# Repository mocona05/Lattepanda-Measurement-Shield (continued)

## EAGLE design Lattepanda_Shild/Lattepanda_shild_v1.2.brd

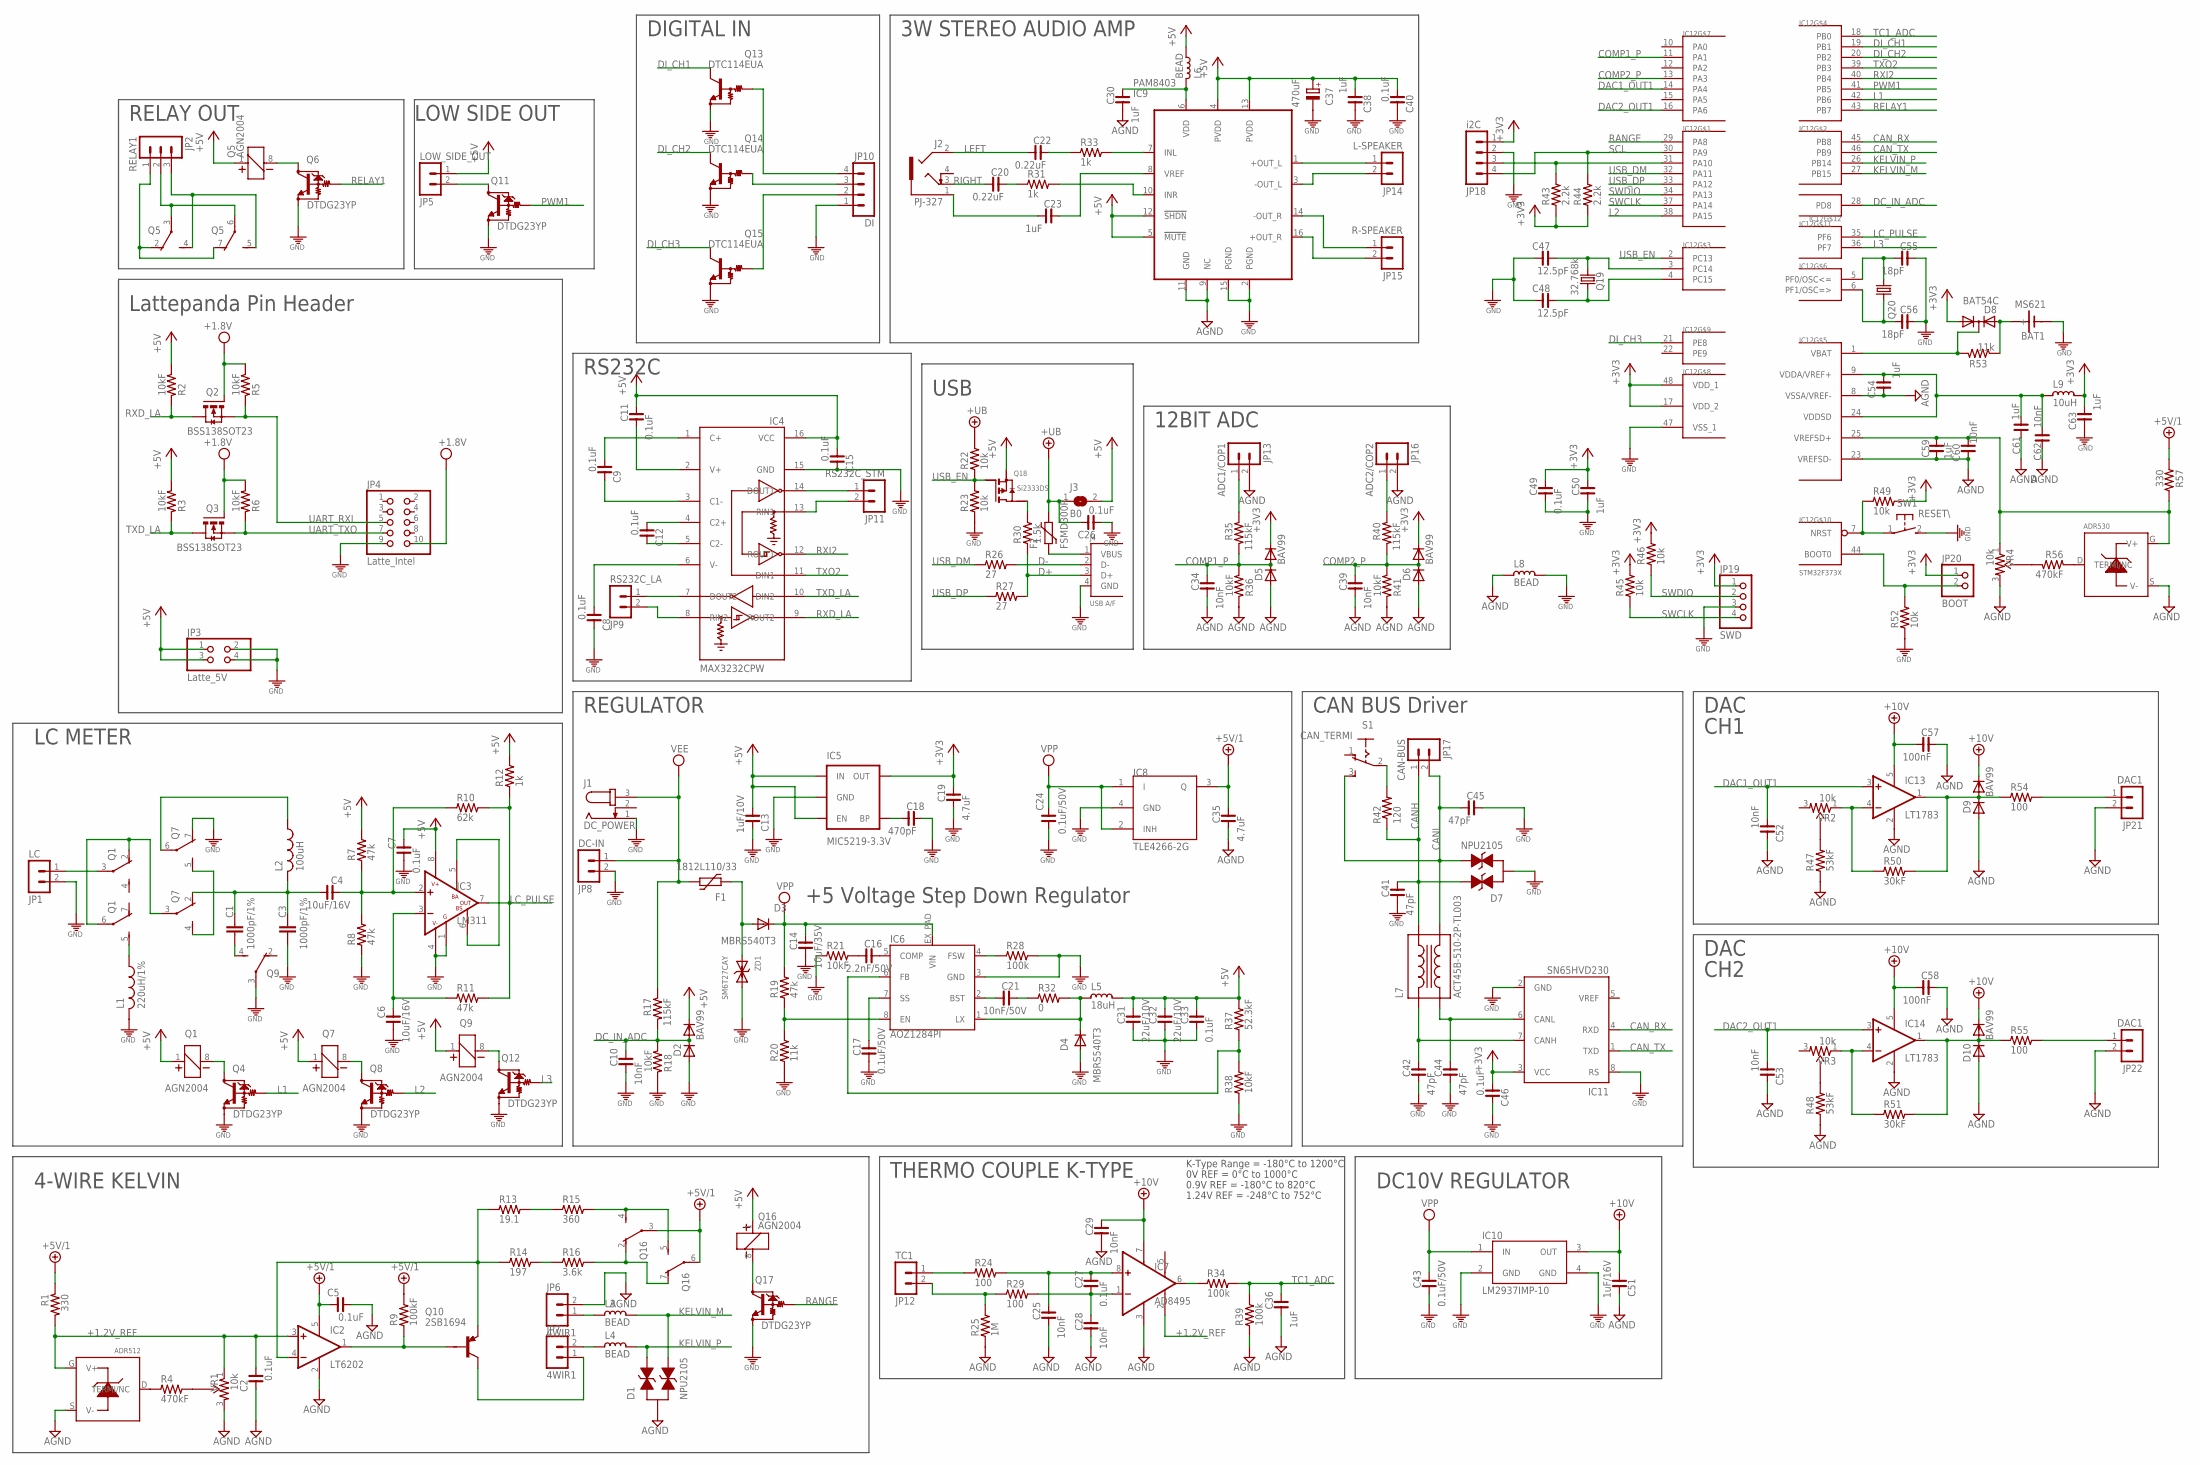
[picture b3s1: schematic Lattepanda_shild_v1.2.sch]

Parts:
BAT1: MS621
C1, C3: 1000pF/1%; C050-025X075
C2, C5, C7, C8, C9, C11, C12, C15, C26, C27, C33, C40, C46, C49: 0.1uF; C0603
C4, C6: 10uF/16V; C3216
C10, C25, C28, C29, C34, C39, C52, C53, C60, C62: 10nF; C0603
C13: 1uF/10V; C0603
C14: 10uF/35V; C3225
C16: 2.2nF/50V; C0603
C17, C43: 0.1uF/50V; C0603
C18: 470pF; C0603
C19, C35: 4.7uF; C2012
C20, C22: 0.22uF; C0603
C21: 10nF/50V; C0603
C23, C30, C36, C38, C50, C54, C59, C61, C63: 1uF; C0603
C24: 0.1uF/50V; C1608-
C31, C32: 22uF/10V; C3216
C37: 470uF; D/7343-31W
C41, C42, C44, C45: 47pF; C0603
C47, C48: 12.5pF; C0603
C51: 1uF/16V; C0603
C55, C56: 18pF; C0603
C57, C58: 100nF; C0603
D1, D7: NPU2105; SOT23
D2, D5, D6, D9, D10: BAV99; SOT23
D3, D4: MBRS540T3; SMC
D8: BAT54C; SOT23
F1: 1812L110/33; 1812L
F2: FSMD300R; 1812L
IC1: ADR512; SOT23
IC2: LT6202; SOT23-5L
IC3: LM311; SO8
IC4: MAX3232CPW; PW_R-PDSO-G16
IC5: MIC5219-3.3V; SOT23-5
IC6: AOZ1284PI; S08-EP1
IC7: AD8495; MSOP8
IC8: TLE4266-2G; SOT223-4
IC9: PAM8403; SOIC16N
IC10: LM2937IMP-10; SOT223
IC11: SN65HVD230; SO8
IC12: STM32F373X; TQFP48
IC13, IC14: LT1783; SOT23-5
IC15: ADR530; SOT23
J1: DC_POWER; SPC4077
J2: PJ-327; PJ-327-2
J3: B0; SJ
J4: USB A/F; USB_AF_SIDE
JP1: LC; ED350V-02P
JP2: RELAY1; ED350V-03P
JP3: Latte_5V; 2X02
JP4: Latte_Intel; 2X05M
JP5: LOW_SIDE_OUT; ED350V-02P
JP6, JP7: 4WIR1; ED350V-02P
JP8: DC-IN; ED350V-02P
JP9: RS232C_LA; ED350V-02P
JP10: DI; 53047-04
JP11: RS232C_STM; ED350V-02P
JP12: TC1; ED350V-02P
JP13: ADC1/COP1; ED350V-02P
JP14: L-SPEAKER; ED350V-02P
JP15: R-SPEAKER; ED350V-02P
JP16: ADC2/COP2; ED350V-02P
JP17: CAN-BUS; ED350V-02P
JP18: i2C; MOLEX5267-04
JP19: SWD; 1X04M
JP20: BOOT; 1X02M
JP21, JP22: DAC1; ED350V-02P
L1: 220uH/1%; 0207/2V
L2: 100uH; 0207/2V
L3, L4, L8: BEAD; L0603
L5: 18uH; SHP1260P-F
L6: BEAD; L0805
L7: ACT45B-510-2P-TL003; ACT45B
L9: 10uH; L0805
Q1, Q5, Q7, Q9, Q16: AGN2004; ANG200X
Q2, Q3: BSS138SOT23; SOT23
Q4, Q6, Q8, Q11, Q12, Q17: DTDG23YP; MPT3
Q10: 2SB1694; SOT323
Q13, Q14, Q15: DTC114EUA; SC59-BEC
Q18: Si2333DS; SOT23
Q19: 32.768k; MC-306
Q20: 8MHz; SMD5032
R1, R57: 330; R0603
R2, R3, R5, R6, R18, R21, R36, R38, R41: 10kF; R0603
R4, R56: 470kF; R0603
R7, R8, R11, R19: 47k; R0603
R9: 100kF; R0603
R10: 62k; R0603
R12, R31, R33: 1k; R0603
R13: 19.1; R0603
R14: 197; R0603
R15: 360; R0603
R16: 3.6k; R0603
R17, R35, R40: 115kF; R0603
R20, R53: 11k; R0603
R22, R23, R45, R46, R49, R52: 10k; R0603
R24, R29, R54, R55: 100; R0603
R25: 1M; R0603
R26, R27: 27; R0603
R28, R34, R39: 100k; R0603
R30: 1.5k; R0603
R32: 0; R0603
R37: 52.3kF; R0603
R42: 120; R0603@1
R43, R44: 2.2k; R0603
R47, R48: 53kF; R0603
R50, R51: 30kF; R0603
S1: CAN_TERMI; 255SB
SW1: RESET\; DTSM-3
VR1, VR4: 10k; 3266W
VR2, VR3: 10k; R-TRIMMER-3313J
ZD1: SM6T27CAY; SMB

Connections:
+1.2V_REF: C2.2, IC1.G (V+), IC2.3 (+IN), IC7.2 (REF), R1.2, VR1.1
+3V3: C19.1, C46.2, C49.1, C50.1, C63.2, D5.S (C), D6.S (C), D8.G (1), IC5.5 (OUT), IC11.3 (VCC), IC12.17 (VDD_2), IC12.48 (VDD_1), JP18.1, JP19.1, JP20.1, L9.1, R43.1, R44.1, R45.2, R46.2, R49.2
+5V: C7.1, C11.1, C13.2, C15.2, C31.1, C32.1, C33.1, C37.+, C38.2, C40.2, D2.S (C), IC3.8 (V+), IC4.16 (VCC), IC5.1 (IN), IC5.3 (EN), IC9.4 (PVDD), IC9.5 (!MUTE), IC9.12 (!SHDN), IC9.13 (PVDD), J3.2, JP3.1, JP3.3, JP5.1, L5.1, L6.1, Q1.1, Q5.1, Q7.1, Q9.1, Q16.1, Q18.S (SOURCE), R2.2, R3.2, R7.2, R12.2, R37.2
+5V/1: C5.1, C35.1, IC2.5 (V+), IC8.3 (Q), Q16.3, Q16.6, R1.1, R9.2, R57.1
+10V: C29.1, C51.2, C57.2, C58.2, D9.S (C), D10.S (C), IC7.7 (V+), IC10.3 (OUT), IC13.5 (V+), IC14.5 (V+)
+UB: C26.1, F2.P$2 (2), J3.1, R22.2
AGND: C2.1, C5.2, C25.2, C28.2, C29.2, C30.2, C34.2, C35.2, C36.2, C39.2, C51.1, C52.1, C53.1, C54.1, C57.1, C58.1, C59.2, C60.1, C61.1, C62.1, D1.D (PIN3), D5.G (A), D6.G (A), D9.G (A), D10.G (A), IC1.S (V-), IC2.2 (V-), IC7.3 (V-), IC9.9 (NC), IC9.11 (GND), IC12.8 (VSSA/VREF-), IC12.23 (VREFSD-), IC13.2 (V-), IC14.2 (V-), IC15.S (V-), JP6.2, JP13.2, JP16.2, JP21.2, JP22.2, L8.2, R25.1, R36.1, R39.1, R41.1, R47.1, R48.1, VR1.3, VR4.3
BOOT1: IC12.44 (BOOT0), JP20.2, R52.2
CANH: C41.1, D7.G (PIN1), JP17.1, L7.4, R42.1
CANL: C45.2, D7.S (PIN2), JP17.2, L7.3, S1.3 (S)
CAN_RX: IC11.4 (RXD), IC12.45 (PB8)
CAN_TX: IC11.1 (TXD), IC12.46 (PB9)
COMP1_P: C34.1, D5.D (AC), IC12.11 (PA1), R35.2, R36.2
COMP2_P: C39.1, D6.D (AC), IC12.13 (PA3), R40.2, R41.2
D+: J4.3 (D+), R27.2, R30.1
D-: J4.2 (D-), R26.2
DAC1_OUT1: C52.2, IC12.14 (PA4), IC13.3 (+IN)
DAC2_OUT1: C53.2, IC12.16 (PA6), IC14.3 (+IN)
DC-IN: D3.A, F1.P$1 (1), ZD1.A
DC_IN_ADC: C10.1, D2.D (AC), IC12.28 (PD8), R17.2, R18.2
DI_CH1: IC12.19 (PB1), Q13.3 (OUT)
DI_CH2: IC12.20 (PB2), Q14.3 (OUT)
DI_CH3: IC12.21 (PE8), Q15.3 (OUT)
GND: BAT1.-, C3.2, C6.2, C7.2, C8.1, C10.2, C13.1, C14.2, C15.1, C17.2, C18.1, C19.2, C24.1, C26.2, C31.2, C32.2, C33.2, C37.-, C38.1, C40.1, C41.2, C42.2, C43.2, C44.2, C45.1, C46.1, C47.1, C48.1, C49.2, C50.2, C55.1, C56.1, C63.1, D2.G (A), D4.A, D7.D (PIN3), IC3.1 (G), IC3.4 (V-), IC4.15 (GND), IC5.2 (GND), IC6.3 (GND), IC8.4 (GND), IC9.2 (PGND), IC9.15 (PGND), IC10.2 (GND), IC10.4 (GND), IC11.2 (GND), IC11.8 (RS), IC12.47 (VSS_1), J1.1, J4.4 (GND), JP1.2, JP3.2, JP3.4, JP4.9, JP8.2, JP10.1, JP18.2, JP19.3, L1.2, L8.1, Q4.EMITTER (GND), Q6.EMITTER (GND), Q7.7 (O), Q8.EMITTER (GND), Q9.3, Q11.EMITTER (GND), Q12.EMITTER (GND), Q13.1 (GND), Q14.1 (GND), Q15.1 (GND), Q17.EMITTER (GND), R8.1, R18.1, R20.1, R21.1, R23.1, R28.2, R38.1, R52.1, SW1.2, ZD1.C (K)
KELVIN_M: D1.S (PIN2), IC12.27 (PB15), L3.1
KELVIN_P: D1.G (PIN1), IC12.26 (PB14), L4.1
L1: IC12.42 (PB6), Q4.BASE (IN)
L2: IC12.38 (PA15), Q8.BASE (IN)
L3: IC12.36 (PF7), Q12.BASE (IN)
LC_PULSE: IC3.7 (OUT), IC12.35 (PF6), R10.2, R11.2, R12.1
LEFT: C22.2, J2.2
unnamed: JP5.2, Q11.COLLECTOR (OUT)
unnamed: IC15.D (TERMI/NC), R56.1
unnamed: IC6.6 (FB), R37.1, R38.2
unnamed: C21.2, IC6.2 (BST)
unnamed: C44.1, IC11.6 (CANL), L7.2
unnamed: C42.1, IC11.7 (CANH), L7.1
unnamed: R14.2, R16.1
unnamed: C21.1, R32.1
unnamed: D4.C, IC6.1 (LX), L5.2, R32.2
unnamed: C16.1, IC6.5 (COMP)
unnamed: C16.2, R21.2
unnamed: R42.2, S1.2
unnamed: R48.2, VR3.2
unnamed: C12.1, IC4.5 (C2-)
unnamed: C12.2, IC4.4 (C2+)
unnamed: C11.2, IC4.2 (V+)
unnamed: IC14.4 (-IN), R51.1, VR3.1
unnamed: D10.D (AC), IC14.1 (OUT), R51.2, R55.1
unnamed: IC6.8 (EN), R19.1, R20.2
unnamed: JP6.1, L3.2
unnamed: IC6.4 (FSW), R28.1
unnamed: JP7.2, L4.2
unnamed: C17.1, IC6.7 (SS)
unnamed: D8.D (3), IC12.1 (VBAT), R53.1
unnamed: C8.2, IC4.6 (V-)
unnamed: C9.2, IC4.1 (C+)
unnamed: IC4.8 (RIN2), JP9.2
unnamed: C9.1, IC4.3 (C1-)
unnamed: IC2.1 (OUT), Q10.2 (B), R9.1
unnamed: Q5.8 (2), Q6.COLLECTOR (OUT)
unnamed: IC4.7 (DOUT2), JP9.1
unnamed: R56.2, VR4.2
unnamed: IC12.7 (NRST), R49.1, SW1.1
unnamed: C56.2, IC12.6 (PF1/OSC=>), Q20.3 (2)
unnamed: IC4.13 (RIN1), JP11.2
unnamed: IC3.5 (BA), IC3.6 (BS)
unnamed: C54.2, C61.2, C62.2, IC12.9 (VDDA/VREF+), IC12.24 (VDDSD), L9.2
unnamed: C6.1, IC3.3 (-IN), R11.1
unnamed: IC4.14 (DOUT1), JP11.1
unnamed: C27.2, C28.1, IC7.1 (-IN), R29.2
unnamed: C25.1, C27.1, IC7.8 (+IN), R24.2
unnamed: IC9.7 (INL), R33.2
unnamed: IC9.1 (+OUT_L), JP14.1
unnamed: JP12.2, R25.2, R29.1
unnamed: JP12.1, R24.1
unnamed: IC7.6 (OUT), R34.1
unnamed: C4.1, IC3.2 (+IN), R7.1, R8.2, R10.1
unnamed: JP7.1, Q10.3 (C)
unnamed: JP13.1, R35.1
unnamed: JP16.1, R40.1
unnamed: IC9.3 (-OUT_L), JP14.2
unnamed: IC9.14 (-OUT_R), JP15.1
unnamed: IC9.16 (+OUT_R), JP15.2
unnamed: IC9.10 (INR), R31.2
unnamed: C23.1, IC9.8 (VREF)
unnamed: C23.2, J2.1
unnamed: C22.1, R33.1
unnamed: F2.P$1 (1), J4.1 (VBUS)
unnamed: JP21.1, R54.2
unnamed: IC1.D (TERMI/NC), R4.1
unnamed: C18.2, IC5.4 (BP)
unnamed: R4.2, VR1.2
unnamed: R13.2, R15.1
unnamed: C20.1, R31.1
unnamed: Q16.8 (2), Q17.COLLECTOR (OUT)
unnamed: Q16.4 (S), Q16.5 (S), R15.2
unnamed: C59.1, C60.2, IC12.25 (VREFSD+), IC15.G (V+), R57.2, VR4.1
unnamed: C30.1, IC9.6 (VDD), L6.2
unnamed: IC2.4 (-IN), Q10.1 (E), R13.1, R14.1
unnamed: IC13.4 (-IN), R50.1, VR2.1
unnamed: Q16.2 (O), Q16.7 (O), R16.2
unnamed: Q7.4 (S), Q7.5 (S)
unnamed: C1.1, C3.1, C4.2, L2.2, Q7.2 (O)
unnamed: Q9.8 (2), Q12.COLLECTOR (OUT)
unnamed: Q7.8 (2), Q8.COLLECTOR (OUT)
unnamed: Q1.2 (O), Q1.6, Q7.3
unnamed: C1.2, Q9.4 (S)
unnamed: L2.1, Q7.6
unnamed: Q1.8 (2), Q4.COLLECTOR (OUT)
unnamed: Q18.D (DRAIN), R30.2
unnamed: L1.1, Q1.5 (S)
unnamed: JP1.1, Q1.3
unnamed: D9.D (AC), IC13.1 (OUT), R50.2, R54.1
unnamed: R47.2, VR2.2
unnamed: JP2.2, Q5.3, Q5.6
unnamed: C55.2, IC12.5 (PF0/OSC<=), Q20.1
unnamed: JP2.1, Q5.2 (O), Q5.7 (O)
unnamed: JP2.3, Q5.4 (S), Q5.5 (S)
unnamed: JP22.1, R55.2
unnamed: IC12.31 (PA10), JP18.3, R43.2
unnamed: BAT1.+, D8.S (2), R53.2
unnamed: JP10.2, Q15.2 (IN)
unnamed: JP10.3, Q14.2 (IN)
unnamed: C47.2, IC12.3 (PC14), Q19.1
unnamed: C48.2, IC12.4 (PC15), Q19.4 (2)
unnamed: JP10.4, Q13.2 (IN)
PWM1: IC12.41 (PB5), Q11.BASE (IN)
RANGE: IC12.29 (PA8), Q17.BASE (IN)
RELAY1: IC12.43 (PB7), Q6.BASE (IN)
RIGHT: C20.2, J2.3
RXD_LA: IC4.9 (ROUT2), Q2.D, R2.1
RXI2: IC4.12 (ROUT1), IC12.40 (PB4)
SCL: IC12.30 (PA9), JP18.4, R44.2
SWCLK: IC12.37 (PA14), JP19.4, R45.1
SWDIO: IC12.34 (PA13), JP19.2, R46.1
TC1_ADC: C36.1, IC12.18 (PB0), R34.2, R39.2
TXD_LA: IC4.10 (DIN2), Q3.D, R3.1
TXO2: IC4.11 (DIN1), IC12.39 (PB3)
UART_RXI: JP4.5, Q2.S, R5.1
UART_TXO: JP4.7, Q3.S, R6.1
USB_DM: IC12.32 (PA11), R26.1
USB_DP: IC12.33 (PA12), R27.1
USB_EN: IC12.2 (PC13), Q18.G (GATE), R22.1, R23.2
VDD: JP4.10, Q2.G, Q3.G, R5.2, R6.2
VEE: F1.P$2 (2), J1.3, JP8.1, R17.1
VPP: C14.1, C24.2, C43.1, D3.C, IC6.EX_PAD (VIN), IC8.1 (I), IC8.2 (INH), IC10.1 (IN), R19.2

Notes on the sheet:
+5 Voltage Step Down Regulator
3W STEREO AUDIO AMP
Lattepanda Pin Header
USB
CAN BUS Driver
4-WIRE KELVIN
K-Type Range = -180°C to 1200°C
1.24V REF = -248°C to 752°C
0.9V REF = -180°C to 820°C
0V REF = 0°C to 1000°C
LC METER
DAC
THERMO COUPLE K-TYPE
RS232C
REGULATOR
DC10V REGULATOR
12BIT ADC
CH1
CH2
LOW SIDE OUT
RELAY OUT
DIGITAL IN

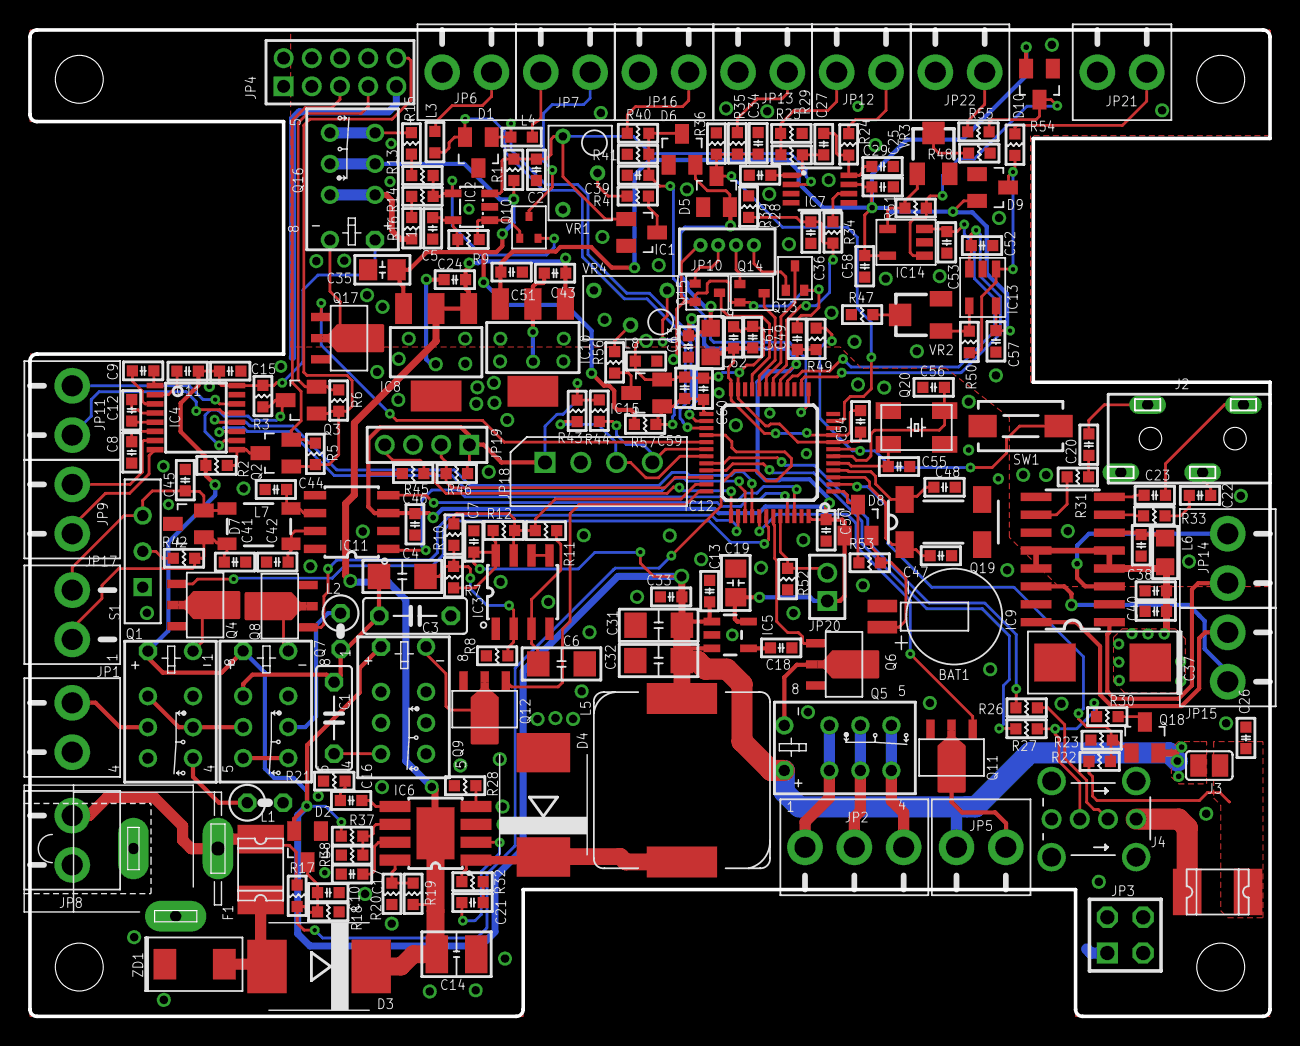
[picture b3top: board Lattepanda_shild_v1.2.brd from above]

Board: 2 copper layers, 88.0 x 70.0 mm, 210 parts (0 on the bottom side), 147 nets.

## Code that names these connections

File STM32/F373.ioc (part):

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Mcu.Name=STM32F373C(8-B-C)Tx
Mcu.Package=LQFP48
Mcu.UserName=STM32F373CCTx
PA1.GPIOParameters=GPIO_Label
PA1.GPIO_Label=ADC1
PA1.Mode=IN1
PA1.Signal=ADC1_IN1
PA10.Mode=I2C
PA10.Signal=I2C2_SDA
PA11.Mode=Device
PA11.Signal=USB_DM
PA12.Mode=Device
PA12.Signal=USB_DP
PA13.Mode=Serial_Wire
PA13.Signal=SYS_JTMS-SWDIO
PA14.Mode=Serial_Wire
PA14.Signal=SYS_JTCK-SWCLK
PA15.GPIOParameters=GPIO_Label
PA15.GPIO_Label=L2
PA15.Signal=GPIO_Output
PA3.GPIOParameters=GPIO_Label
PA3.GPIO_Label=ADC2
PA3.Mode=IN3
PA3.Signal=ADC1_IN3
PA4.GPIOParameters=GPIO_Label
PA4.GPIO_Label=DAC1
PA4.Signal=COMP_DAC11_group
PA5.GPIOParameters=GPIO_Label
PA5.GPIO_Label=C_CTL
PA5.Signal=GPIO_Output
PA6.GPIOParameters=GPIO_Label
PA6.GPIO_Label=DAC2
PA6.Signal=COMP_DAC21_group
PA8.GPIOParameters=GPIO_Label
PA8.GPIO_Label=RANGE
PA8.Signal=GPIO_Output
PA9.Mode=I2C
PA9.Signal=I2C2_SCL
PB0.GPIOParameters=GPIO_Label
PB0.GPIO_Label=TC1
PB0.Mode=IN6-Single-Ended
PB0.Signal=SDADC1_AIN6P
PB1.GPIOParameters=GPIO_PuPd,GPIO_Label
PB1.GPIO_Label=DI_CH1
PB1.GPIO_PuPd=GPIO_PULLUP
PB1.Signal=GPIO_Input
PB14.GPIOParameters=GPIO_Label
PB14.GPIO_Label=KELVIN_P
PB14.Mode=IN8-Differential
PB14.Signal=SDADC3_AIN8P
PB15.GPIOParameters=GPIO_Label
PB15.GPIO_Label=KELVIN_M
PB15.Mode=IN8-Differential
PB15.Signal=SDADC3_AIN8M
PB2.GPIOParameters=GPIO_PuPd,GPIO_Label
PB2.GPIO_Label=DI_CH2
PB2.GPIO_PuPd=GPIO_PULLUP
PB2.Signal=GPIO_Input
PB3.Mode=Asynchronous
PB3.Signal=USART2_TX
PB4.Mode=Asynchronous
PB4.Signal=USART2_RX
PB5.GPIOParameters=GPIO_Label
PB5.GPIO_Label=PWM1
PB5.Signal=S_TIM3_CH2
PB6.GPIOParameters=GPIO_Label
PB6.GPIO_Label=L1
PB6.Signal=GPIO_Output
PB7.GPIOParameters=GPIO_Label
PB7.GPIO_Label=RELAY
PB7.Signal=GPIO_Output
PB8.Mode=Master
PB8.Signal=CAN_RX
PB9.Mode=Master
PB9.Signal=CAN_TX
PC13.GPIOParameters=GPIO_Speed,PinState,GPIO_Label,GPIO_ModeDefaultOutputPP
PC13.GPIO_Label=USB_EN
PC13.GPIO_ModeDefaultOutputPP=GPIO_MODE_OUTPUT_PP
PC13.GPIO_Speed=GPIO_SPEED_FREQ_LOW
PC13.PinState=GPIO_PIN_RESET
PC13.Signal=GPIO_Output
PC14-OSC32_IN.Mode=LSE-External-Oscillator
PC14-OSC32_IN.Signal=RCC_OSC32_IN
PC15-OSC32_OUT.Mode=LSE-External-Oscillator
PC15-OSC32_OUT.Signal=RCC_OSC32_OUT
PE8.GPIOParameters=GPIO_PuPd,GPIO_Label
PE8.GPIO_Label=DI_CH3
PE8.GPIO_PuPd=GPIO_PULLUP
PE8.Signal=GPIO_Input
PF0-OSC_IN.Mode=HSE-External-Oscillator
PF0-OSC_IN.Signal=RCC_OSC_IN
PF1-OSC_OUT.Mode=HSE-External-Oscillator
PF1-OSC_OUT.Signal=RCC_OSC_OUT
PF6.GPIOParameters=GPIO_Speed,GPIO_PuPd,GPIO_Label
PF6.GPIO_Label=LC_PULSE
PF6.GPIO_PuPd=GPIO_PULLUP
PF6.GPIO_Speed=GPIO_SPEED_FREQ_MEDIUM
PF6.Signal=S_TIM4_CH4
PF7.GPIOParameters=GPIO_Label
PF7.GPIO_Label=L3
PF7.Signal=GPIO_Output
RCC.HSEPLLFreq_Value=8000000
RCC.HSE_VALUE=8000000
RCC.SYSCLKFreq_VALUE=72000000
RCC.SYSCLKSource=RCC_SYSCLKSOURCE_PLLCLK
board=F373

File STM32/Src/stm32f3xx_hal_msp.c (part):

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    __HAL_RCC_ADC1_CLK_ENABLE();
  
    /**ADC1 GPIO Configuration    
    PA1     ------> ADC1_IN1
    PA3     ------> ADC1_IN3 
    */
    GPIO_InitStruct.Pin = ADC1_Pin|ADC2_Pin;
    GPIO_InitStruct.Mode = GPIO_MODE_ANALOG;
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    __HAL_RCC_ADC1_CLK_DISABLE();
  
    /**ADC1 GPIO Configuration    
    PA1     ------> ADC1_IN1
    PA3     ------> ADC1_IN3 
    */
    HAL_GPIO_DeInit(GPIOA, ADC1_Pin|ADC2_Pin);

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    __HAL_RCC_CAN1_CLK_ENABLE();
  
    /**CAN GPIO Configuration    
    PB8     ------> CAN_RX
    PB9     ------> CAN_TX 
    */
    GPIO_InitStruct.Pin = GPIO_PIN_8|GPIO_PIN_9;
    GPIO_InitStruct.Mode = GPIO_MODE_AF_PP;
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    __HAL_RCC_CAN1_CLK_DISABLE();
  
    /**CAN GPIO Configuration    
    PB8     ------> CAN_RX
    PB9     ------> CAN_TX 
    */
    HAL_GPIO_DeInit(GPIOB, GPIO_PIN_8|GPIO_PIN_9);

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    __HAL_RCC_DAC1_CLK_ENABLE();
  
    /**DAC1 GPIO Configuration    
    PA4     ------> DAC1_OUT1 
    */
    GPIO_InitStruct.Pin = DAC1_Pin;
    GPIO_InitStruct.Mode = GPIO_MODE_ANALOG;
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    __HAL_RCC_DAC2_CLK_ENABLE();
  
    /**DAC2 GPIO Configuration    
    PA6     ------> DAC2_OUT1 
    */
    GPIO_InitStruct.Pin = DAC2_Pin;
    GPIO_InitStruct.Mode = GPIO_MODE_ANALOG;
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    __HAL_RCC_DAC1_CLK_DISABLE();
  
    /**DAC1 GPIO Configuration    
    PA4     ------> DAC1_OUT1 
    */
    HAL_GPIO_DeInit(DAC1_GPIO_Port, DAC1_Pin);

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    __HAL_RCC_DAC2_CLK_DISABLE();
  
    /**DAC2 GPIO Configuration    
    PA6     ------> DAC2_OUT1 
    */
    HAL_GPIO_DeInit(DAC2_GPIO_Port, DAC2_Pin);

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  /* USER CODE END I2C2_MspInit 0 */
  
    /**I2C2 GPIO Configuration    
    PA9     ------> I2C2_SCL
    PA10     ------> I2C2_SDA 
    */
    GPIO_InitStruct.Pin = GPIO_PIN_9|GPIO_PIN_10;
    GPIO_InitStruct.Mode = GPIO_MODE_AF_OD;
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    __HAL_RCC_I2C2_CLK_DISABLE();
  
    /**I2C2 GPIO Configuration    
    PA9     ------> I2C2_SCL
    PA10     ------> I2C2_SDA 
    */
    HAL_GPIO_DeInit(GPIOA, GPIO_PIN_9|GPIO_PIN_10);

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    __HAL_RCC_SDADC1_CLK_ENABLE();
  
    /**SDADC1 GPIO Configuration    
    PB0     ------> SDADC1_AIN6P 
    */
    GPIO_InitStruct.Pin = TC1_Pin;
    GPIO_InitStruct.Mode = GPIO_MODE_ANALOG;
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    __HAL_RCC_SDADC3_CLK_ENABLE();
  
    /**SDADC3 GPIO Configuration    
    PB14     ------> SDADC3_AIN8P
    PB15     ------> SDADC3_AIN8M 
    */
    GPIO_InitStruct.Pin = KELVIN_P_Pin|KELVIN_M_Pin;
    GPIO_InitStruct.Mode = GPIO_MODE_ANALOG;
    GPIO_InitStruct.Pull = GPIO_NOPULL;
    HAL_GPIO_Init(GPIOB, &GPIO_InitStruct);
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    __HAL_RCC_SDADC1_CLK_DISABLE();
  
    /**SDADC1 GPIO Configuration    
    PB0     ------> SDADC1_AIN6P 
    */
    HAL_GPIO_DeInit(TC1_GPIO_Port, TC1_Pin);

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    __HAL_RCC_SDADC3_CLK_DISABLE();
  
    /**SDADC3 GPIO Configuration    
    PB14     ------> SDADC3_AIN8P
    PB15     ------> SDADC3_AIN8M 
    */
    HAL_GPIO_DeInit(GPIOB, KELVIN_P_Pin|KELVIN_M_Pin);

    /* SDADC3 DMA DeInit */
    HAL_DMA_DeInit(hsdadc->hdma);
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    __HAL_RCC_TIM4_CLK_ENABLE();
  
    /**TIM4 GPIO Configuration    
    PF6     ------> TIM4_CH4 
    */
    GPIO_InitStruct.Pin = LC_PULSE_Pin;
    GPIO_InitStruct.Mode = GPIO_MODE_AF_PP;
    GPIO_InitStruct.Pull = GPIO_PULLUP;
    GPIO_InitStruct.Speed = GPIO_SPEED_FREQ_MEDIUM;
    GPIO_InitStruct.Alternate = GPIO_AF2_TIM4;
    HAL_GPIO_Init(LC_PULSE_GPIO_Port, &GPIO_InitStruct);

    /* TIM4 interrupt Init */
    HAL_NVIC_SetPriority(TIM4_IRQn, 5, 0);
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  /* USER CODE END TIM3_MspPostInit 0 */
  
    /**TIM3 GPIO Configuration    
    PB5     ------> TIM3_CH2 
    */
    GPIO_InitStruct.Pin = PWM1_Pin;
    GPIO_InitStruct.Mode = GPIO_MODE_AF_PP;
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    __HAL_RCC_TIM4_CLK_DISABLE();
  
    /**TIM4 GPIO Configuration    
    PF6     ------> TIM4_CH4 
    */
    HAL_GPIO_DeInit(LC_PULSE_GPIO_Port, LC_PULSE_Pin);

    /* TIM4 interrupt DeInit */
    HAL_NVIC_DisableIRQ(TIM4_IRQn);
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    __HAL_RCC_USART2_CLK_ENABLE();
  
    /**USART2 GPIO Configuration    
    PB3     ------> USART2_TX
    PB4     ------> USART2_RX 
    */
    GPIO_InitStruct.Pin = GPIO_PIN_3|GPIO_PIN_4;
    GPIO_InitStruct.Mode = GPIO_MODE_AF_PP;
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    __HAL_RCC_USART2_CLK_DISABLE();
  
    /**USART2 GPIO Configuration    
    PB3     ------> USART2_TX
    PB4     ------> USART2_RX 
    */
    HAL_GPIO_DeInit(GPIOB, GPIO_PIN_3|GPIO_PIN_4);

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
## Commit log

2017-07-23 stm32 beta 0.1 source
2017-07-23 Mavlink xml upload
2017-07-23 readme update1
2017-07-23 RTC update error complit
2017-07-23 redme update
2017-07-24 SDADC&ADC Frequency Change
2017-07-24 compile dir error patch
2017-07-25 Kelvin Zero Calibration modity
2017-07-25 SDADC mean DSP
2017-07-25 Kelvin Zero Calibration patch
2017-07-26 Kelvin zeor calibraton
2017-07-26 kelvin calculation patch
2021-07-17 notebook change
2023-07-31 pcb upload

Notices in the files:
STM32/Src/stm32f3xx_hal_msp.c:
Copyright (c) 2017 STMicroelectronics International N.V.
All rights reserved.
(C) COPYRIGHT STMicroelectronics *****END OF FILE
